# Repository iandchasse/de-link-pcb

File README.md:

# Silkscreen

**An open-source, open-hardware e-reader base board.**
Display-agnostic · case-agnostic · firmware-agnostic · battery-agnostic.

Successor to [de-link](https://de-link.me). Designed in **KiCad 9.0.6**.

Silkscreen is a base board for e-ink development: one 2-layer PCB that aims to drive
essentially any 24-pin SPI e-paper panel, from any battery, in any enclosure, under any
firmware — so the interesting work (display, case, software) isn't gated on redesigning power
and interface electronics every time.

Current full plots: **[schematic PDF](docs/silkscreen_pcb_schematic.pdf)** ·
**[PCB PDF](docs/silkscreen_pcb.pdf)**.

---

## At a glance

| | |
|---|---|
| **MCU** | ESP32-S3-WROOM-1 (**N8R8**, 8 MB octal PSRAM), native USB — no UART bridge |
| **Display** | 24-pin 0.5 mm ZIF for SPI e-paper; primary target 4.26" GDEQ426T82 family; panel-driven charge pump generates the ±15–22 V rails |
| **Frontlight** | TPS923610 constant-current boost, warm/cool CCT blending via a single GPIO + inverter |
| **Touch** | Optional I²C capacitive touch (for `-FT01C`-class panels) with a 0 Ω pin-swap mux |
| **Power** | USB-C in → TP4056 charger → DW01A + FS8205A cell protection → TPS2116 priority mux → TLV75533P 3V3 LDO |
| **Battery** | Bring-your-own single-cell LiPo; full on-board protection makes a bare cell safe |
| **Storage** | microSD in 4-bit SDMMC, power-gated |
| **Input** | 8 buttons on two ADC resistor ladders + power/boot/reset |
| **RTC** | DS3231MZ (±2 ppm), VBAT-only mode |
| **Board** | 2-layer, 60 × 111 mm, 1 oz Cu, 173 components |

Full block-by-block description: **[docs/HARDWARE.md](docs/HARDWARE.md)**.
Schematic review, margins and design rationale: **[DESIGN_REVIEW.md](DESIGN_REVIEW.md)**.

---

## Repository layout

```
silkscreen_pcb.kicad_pro / .kicad_sch / .kicad_pcb   KiCad 9 project
sym-lib-table / fp-lib-table                          project-local library tables
KiCad/9.0/3rdparty/                                   vendored symbols/footprints/3D models
docs/HARDWARE.md                                      hardware documentation
DESIGN_REVIEW.md                                      schematic + layout review
fabrication/                                          BOM, assembly data, how-to (gerbers gitignored)
LICENSE                                               CERN-OHL-S v2
```

## Building the board

You need **KiCad 9.0.x** (the files are 9.0 format; opening in 10.x upgrades them one-way).

### Fabrication (bare board)

Generate a gerber + drill set (JLCPCB, PCBWay and NextPCB all accept the same standard set):

```bash
kicad-cli pcb export gerbers -o fabrication/gerbers/ \
  --layers F.Cu,B.Cu,F.Mask,B.Mask,F.SilkS,B.SilkS,F.Paste,B.Paste,Edge.Cuts \
  --no-protel-ext --subtract-soldermask silkscreen_pcb.kicad_pcb
kicad-cli pcb export drill -o fabrication/gerbers/ --format excellon \
  --drill-origin absolute --excellon-units mm --excellon-separate-th silkscreen_pcb.kicad_pcb
```

Zip `fabrication/gerbers/` and upload. Board is 2-layer, 1.6 mm, 1 oz copper; outline on `Edge.Cuts`.

### Assembly

```bash
kicad-cli pcb export pos -o fabrication/assembly/cpl.csv --format csv --units mm --side both silkscreen_pcb.kicad_pcb
```

- **JLCPCB:** prefer the KiCad **Fabrication Toolkit** plugin — it applies JLC's part-rotation
  database and fills LCSC part numbers automatically. See [`fabrication/README.md`](fabrication/README.md).
- **PCBWay / NextPCB:** upload the gerber zip + the centroid + [`fabrication/BOM.csv`](fabrication/BOM.csv);
  they quote against the manufacturer part numbers.

See **[fabrication/README.md](fabrication/README.md)** for the full per-house process and caveats.

## Bill of materials

**[fabrication/BOM.md](fabrication/BOM.md)** — full BOM with manufacturers, MPNs, DigiKey/LCSC
links, LCSC-cheaper alternates, and per-part pricing with quantity break costs (board + a
"complete build" section covering PCB fab, display and battery).

## Documentation

- **[docs/HARDWARE.md](docs/HARDWARE.md)** — how every block works, GPIO map, design themes.
- **[DESIGN_REVIEW.md](DESIGN_REVIEW.md)** — net-by-net schematic review, margin analysis, and
  the layout spot-review.

---

## License

Hardware licensed under the **CERN Open Hardware Licence Version 2 – Strongly Reciprocal
(CERN-OHL-S-2.0)** — see [LICENSE](LICENSE).

> Copyright © 2026 idc LLC.
> This source describes Open Hardware and is licensed under the CERN-OHL-S v2.
> You may redistribute and modify this source and make products using it under the terms of the
> CERN-OHL-S v2 (https://ohwr.org/cern_ohl_s_v2.txt). This source is distributed WITHOUT ANY
> EXPRESS OR IMPLIED WARRANTY, INCLUDING OF MERCHANTABILITY, SATISFACTORY QUALITY AND FITNESS FOR
> A PARTICULAR PURPOSE. Please see the CERN-OHL-S v2 for applicable conditions.

`SPDX-License-Identifier: CERN-OHL-S-2.0`

Third-party component library files (from SnapEDA / Ultra Librarian / SamacSys) retain their own
terms and are not covered by the project license — see
[fabrication/THIRD_PARTY.md](fabrication/THIRD_PARTY.md).

Predecessor project: [de-link.me](https://de-link.me).

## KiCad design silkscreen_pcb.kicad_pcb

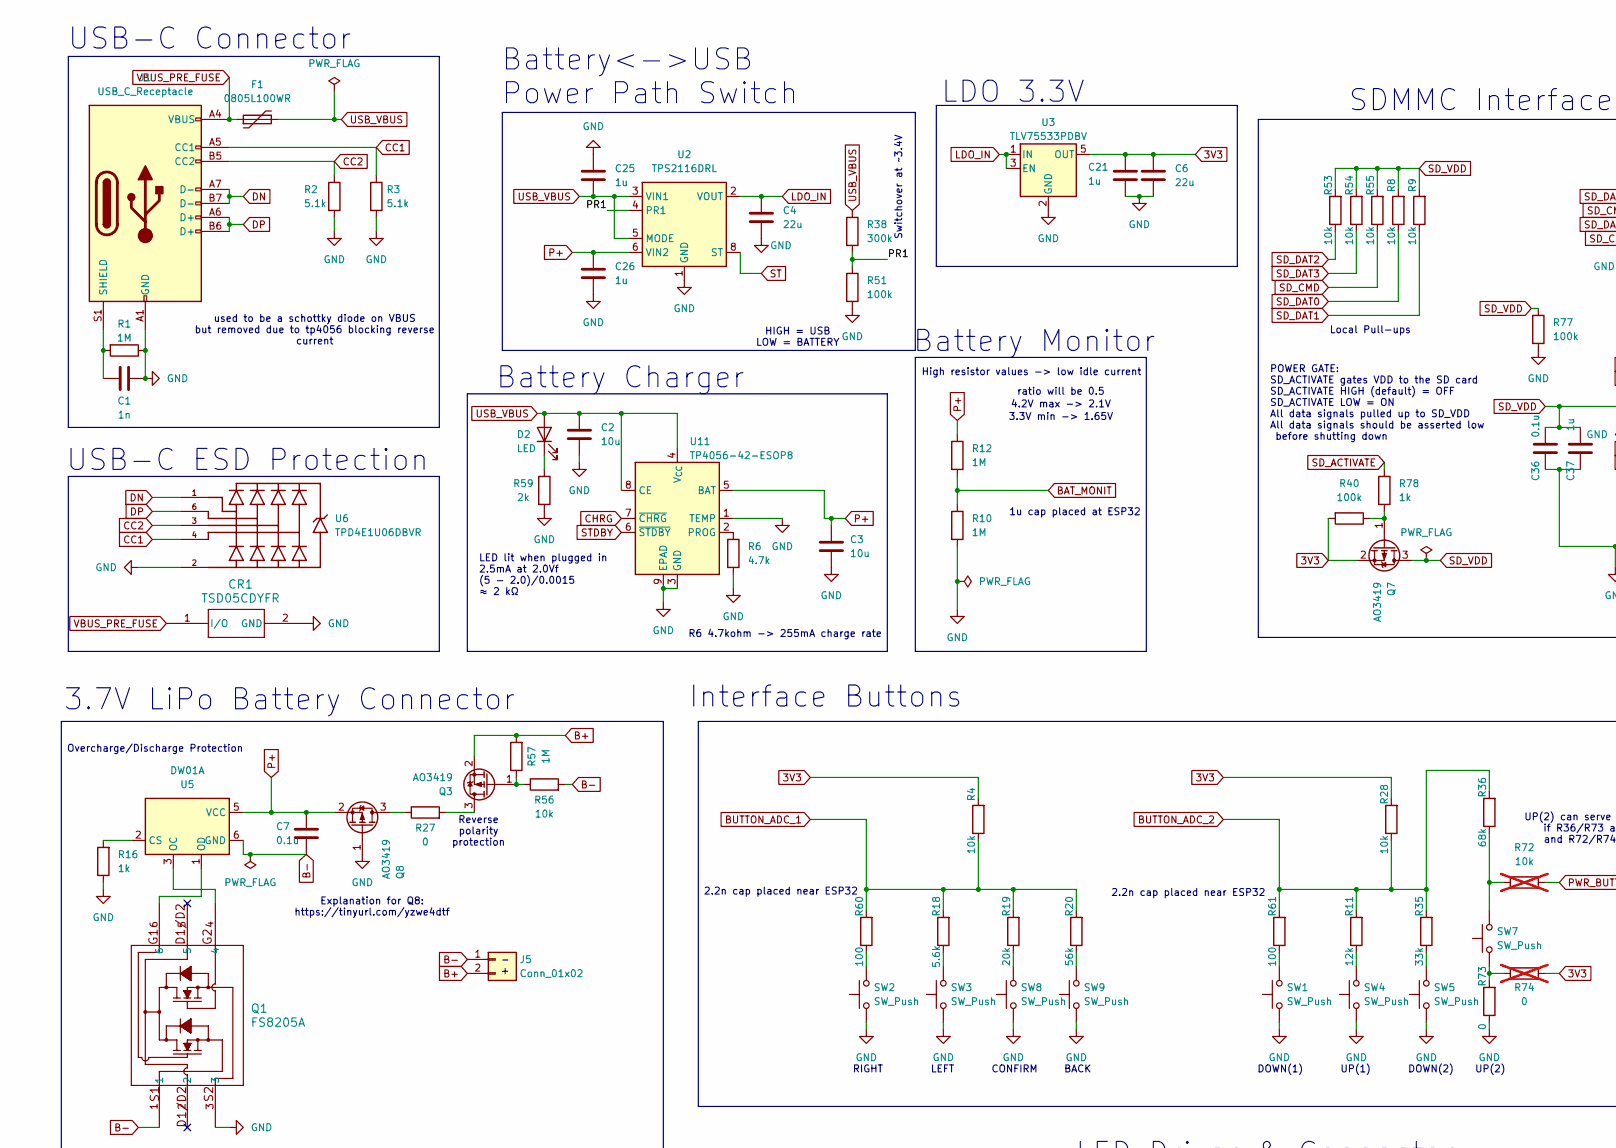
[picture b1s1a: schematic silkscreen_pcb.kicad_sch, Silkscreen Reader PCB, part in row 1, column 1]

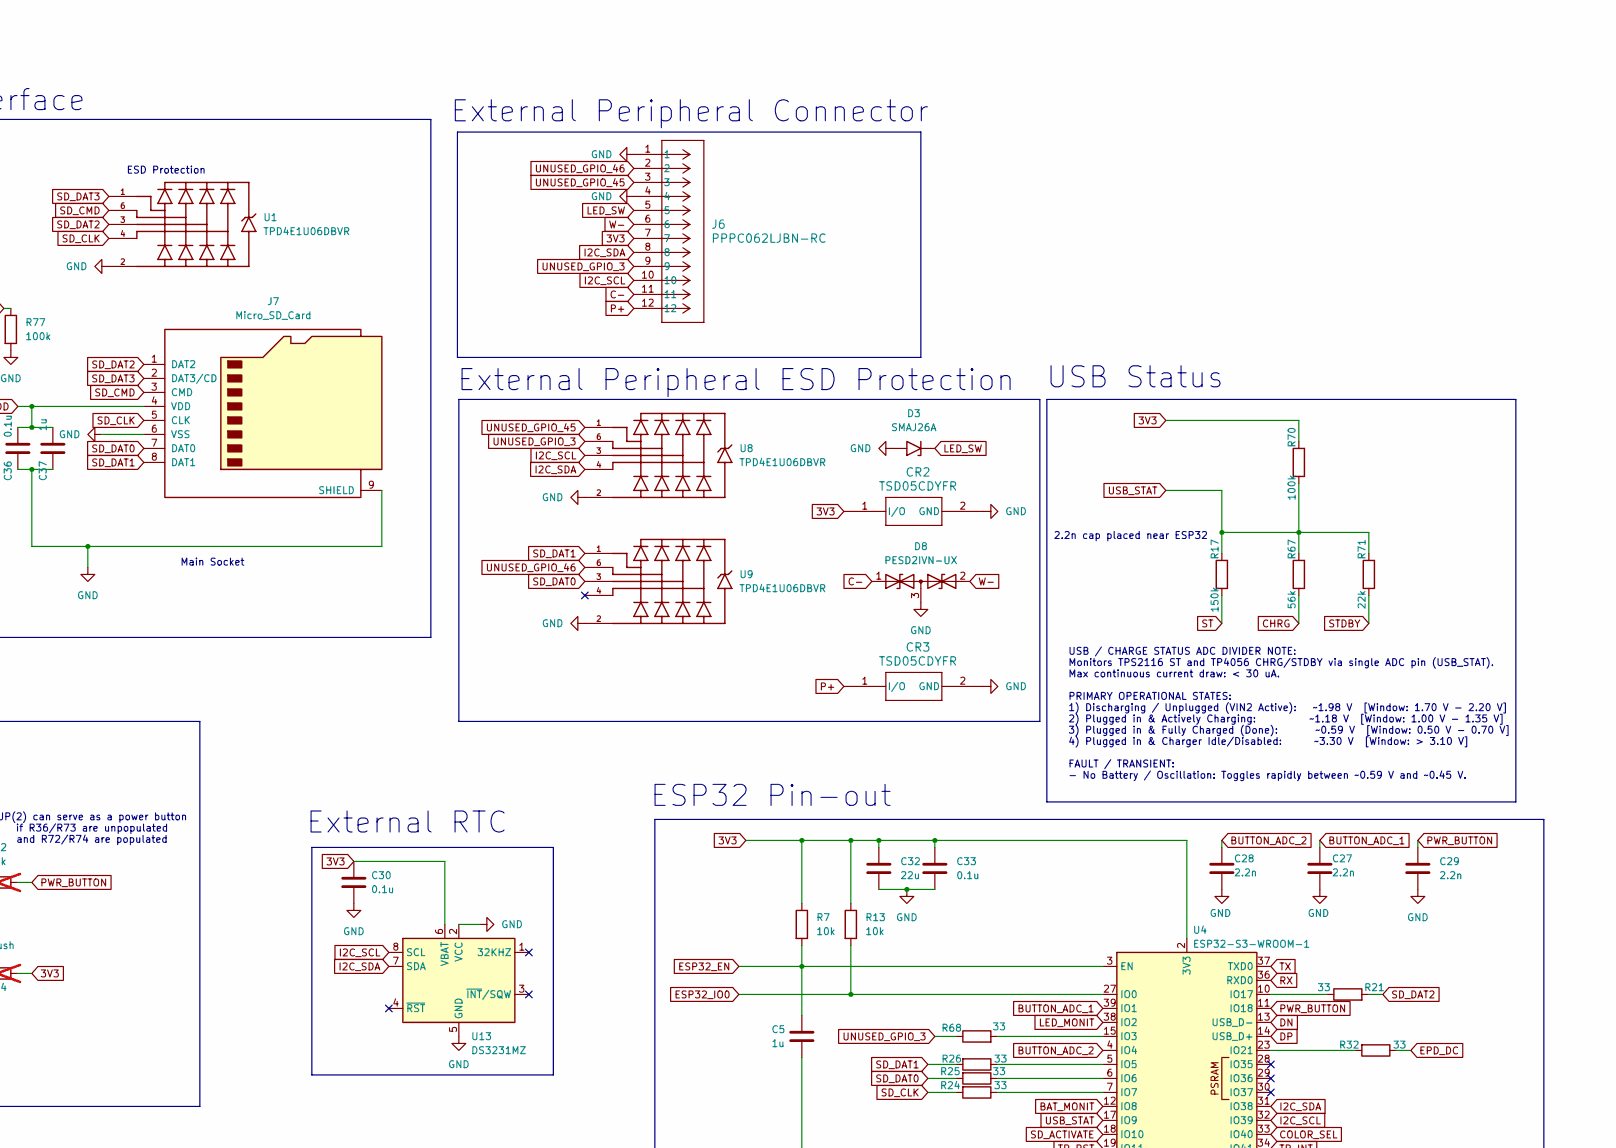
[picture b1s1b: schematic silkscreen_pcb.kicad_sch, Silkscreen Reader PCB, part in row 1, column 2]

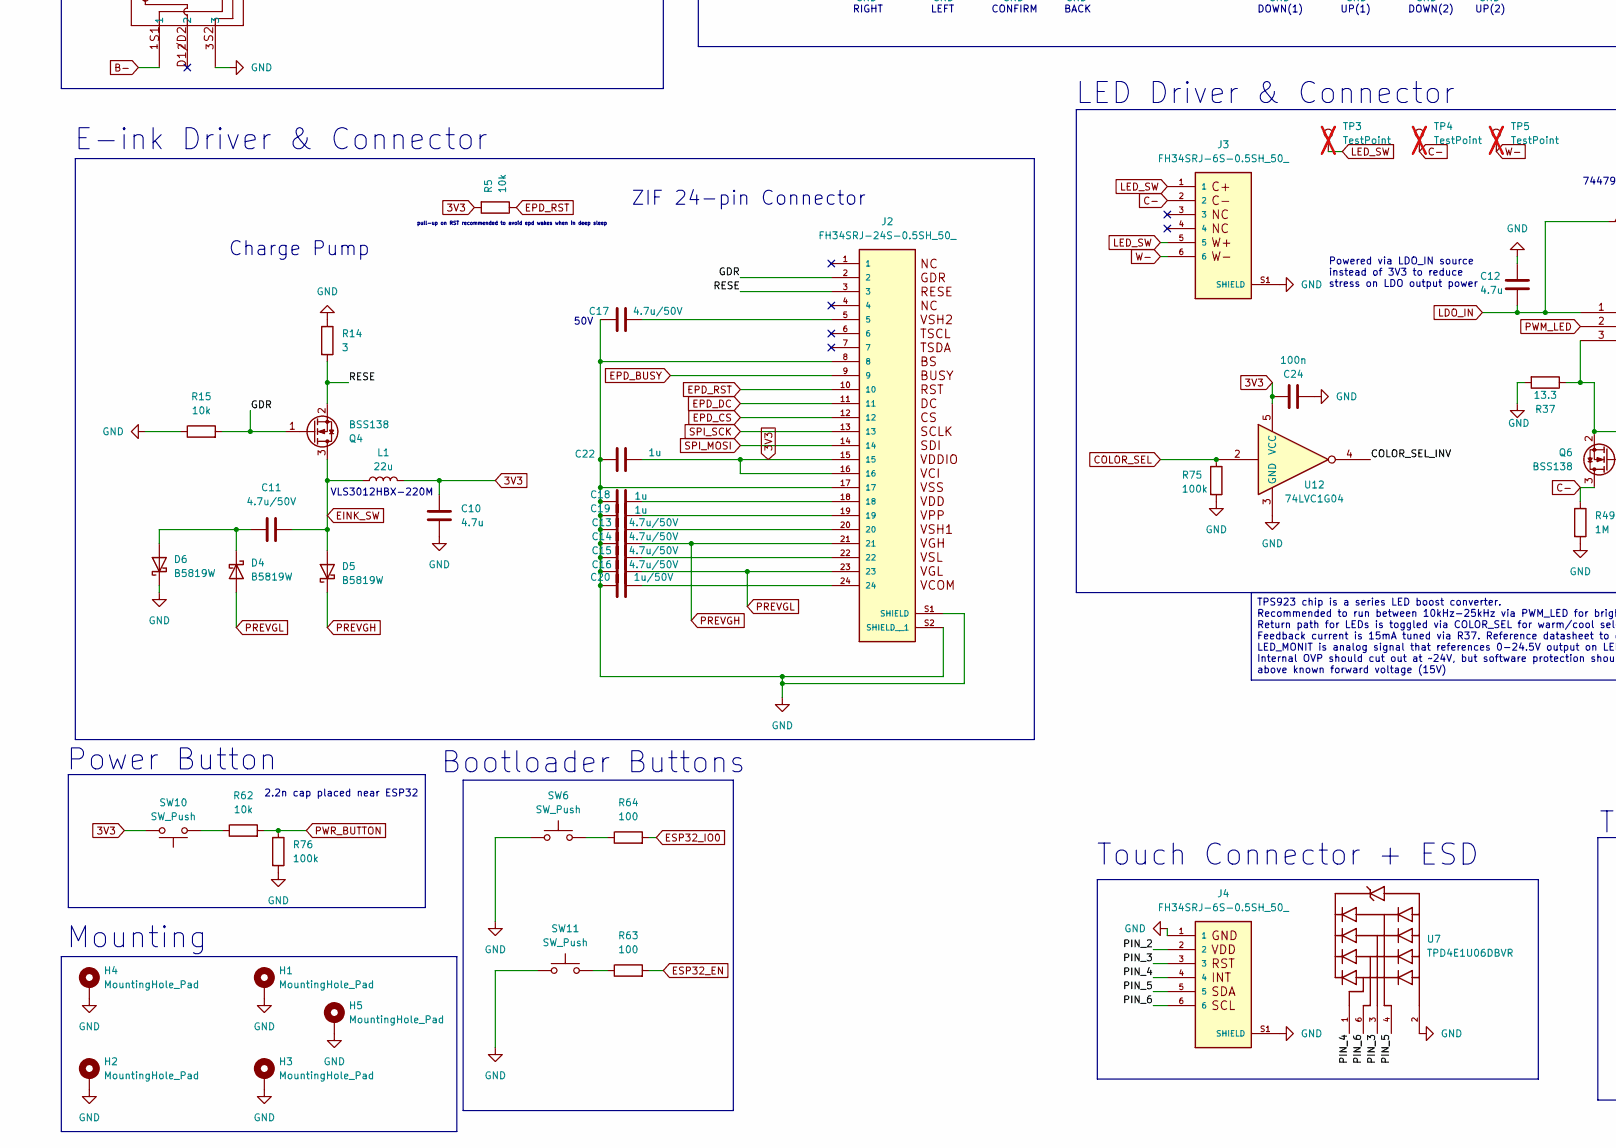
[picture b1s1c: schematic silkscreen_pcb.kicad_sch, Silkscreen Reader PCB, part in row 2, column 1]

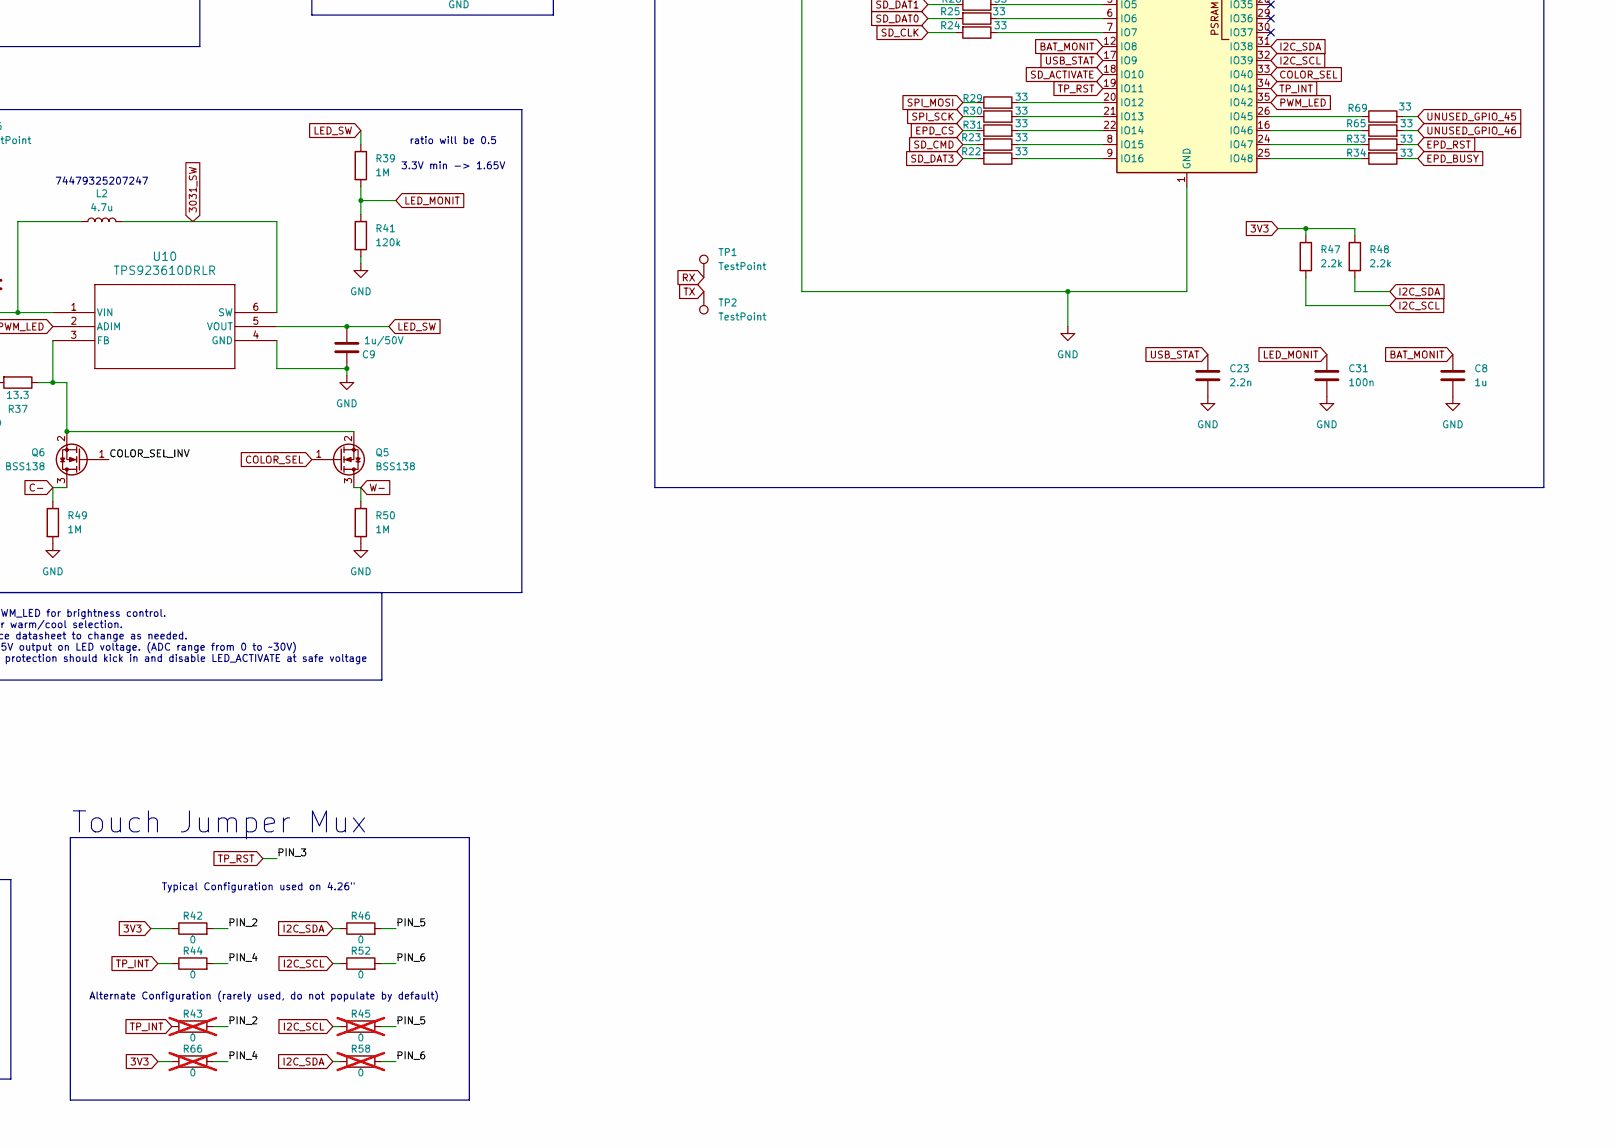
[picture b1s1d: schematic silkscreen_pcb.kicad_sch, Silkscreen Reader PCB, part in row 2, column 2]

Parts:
C1: 1n; C_0603_1608Metric_Pad1.08x0.95mm_HandSolder
C2, C3: 10u; C_0603_1608Metric_Pad1.08x0.95mm_HandSolder
C4, C6, C32: 22u; C_0805_2012Metric_Pad1.18x1.45mm_HandSolder
C5, C8, C21, C22, C25, C26, C37: 1u; C_0603_1608Metric_Pad1.08x0.95mm_HandSolder
C7, C30, C33, C36: 0.1u; C_0603_1608Metric_Pad1.08x0.95mm_HandSolder
C9, C20: 1u/50V; C_0805_2012Metric_Pad1.18x1.45mm_HandSolder
C10, C12: 4.7u; C_0603_1608Metric_Pad1.08x0.95mm_HandSolder
C11, C13, C14, C15, C16, C17: 4.7u/50V; C_0805_2012Metric_Pad1.18x1.45mm_HandSolder
C18, C19: 1u; C_0805_2012Metric_Pad1.18x1.45mm_HandSolder
C23, C27, C28, C29: 2.2n; C_0603_1608Metric_Pad1.08x0.95mm_HandSolder
C24, C31: 100n; C_0603_1608Metric_Pad1.08x0.95mm_HandSolder
CR1, CR2, CR3: TSD05CDYFR; D_SOD-323_HandSoldering
D2: LED; LED_1206_3216Metric_Pad1.42x1.75mm_HandSolder
D3: SMAJ26A; D_SMA
D4, D5, D6: B5819W; D_SOD-123
D8: PESD2IVN-UX; SOT-323_SC-70_Handsoldering
F1: 0805L100WR; Fuse_0805_2012Metric_Pad1.15x1.40mm_HandSolder
H1, H2, H3, H4, H5: MountingHole_Pad; MountingHole_2.2mm_M2_DIN965_Pad_TopBottom
J1: USB_C_Receptacle; USB_C_Receptacle_GCT_USB4085
J2: FH34SRJ-24S-0.5SH_50_; HRS_FH34SRJ-24S-0.5SH_50_
J3, J4: FH34SRJ-6S-0.5SH_50_; HRS_FH34SRJ-6S-0.5SH_50_; DigiKey_Part_Number H125773CT-ND
J5: Conn_01x02; JST_PH_S2B-PH-K_1x02_P2.00mm_Horizontal
J6: PPPC062LJBN-RC; CONN_PPPC062LJBN-RC_SUL
J7: Micro_SD_Card; microSD_HC_Hirose_DM3AT-SF-PEJM5
L1: 22u; IND_SRN3010C-100M
L2: 4.7u; L_1008_2520Metric_Pad1.43x2.20mm_HandSolder
Q1: FS8205A; SOT-23-6_Handsoldering
Q3, Q7, Q8: AO3419; SOT-23_Handsoldering
Q4, Q5, Q6: BSS138; SOT-23
R1, R10, R12, R39, R49, R50, R57: 1M; R_0603_1608Metric_Pad0.98x0.95mm_HandSolder
R2, R3: 5.1k; R_0603_1608Metric_Pad0.98x0.95mm_HandSolder
R4, R5, R7, R8, R9, R13, R15, R28, R53, R54, R55, R56, R62: 10k; R_0603_1608Metric_Pad0.98x0.95mm_HandSolder
R6: 4.7k; R_0603_1608Metric_Pad0.98x0.95mm_HandSolder
R11: 12k; R_0603_1608Metric_Pad0.98x0.95mm_HandSolder
R14: 3; R_0603_1608Metric_Pad0.98x0.95mm_HandSolder
R16, R78: 1k; R_0603_1608Metric_Pad0.98x0.95mm_HandSolder
R17: 150k; R_0603_1608Metric_Pad0.98x0.95mm_HandSolder
R18: 5.6k; R_0603_1608Metric_Pad0.98x0.95mm_HandSolder
R19: 20k; R_0603_1608Metric_Pad0.98x0.95mm_HandSolder
R20, R67: 56k; R_0603_1608Metric_Pad0.98x0.95mm_HandSolder
R21, R22, R23, R24, R25, R26, R29, R30, R31, R32, R33, R34, R65, R68, R69: 33; R_0603_1608Metric_Pad0.98x0.95mm_HandSolder
R27, R42, R44, R46, R52, R73: 0; R_0603_1608Metric_Pad0.98x0.95mm_HandSolder
R35: 33k; R_0603_1608Metric_Pad0.98x0.95mm_HandSolder
R36: 68k; R_0603_1608Metric_Pad0.98x0.95mm_HandSolder
R37: 13.3; R_0603_1608Metric_Pad0.98x0.95mm_HandSolder
R38: 300k; R_0603_1608Metric_Pad0.98x0.95mm_HandSolder
R40, R51, R70, R75, R76, R77: 100k; R_0603_1608Metric_Pad0.98x0.95mm_HandSolder
R41: 120k; R_0603_1608Metric_Pad0.98x0.95mm_HandSolder
R43, R45, R58, R66, R74: 0; R_0603_1608Metric_Pad0.98x0.95mm_HandSolder; not fitted
R47, R48: 2.2k; R_0603_1608Metric_Pad0.98x0.95mm_HandSolder
R59: 2k; R_0603_1608Metric_Pad0.98x0.95mm_HandSolder
R60, R61, R63, R64: 100; R_0603_1608Metric_Pad0.98x0.95mm_HandSolder
R71: 22k; R_0603_1608Metric_Pad0.98x0.95mm_HandSolder
R72: 10k; R_0603_1608Metric_Pad0.98x0.95mm_HandSolder; not fitted
SW1, SW2, SW3, SW4, SW5, SW7, SW8, SW9, SW10, SW11: SW_Push; MJTP1117
SW6: SW_Push; SW_PUSH_1P1T_6x3.5mm_H4.3_APEM_MJTP1243
TP1, TP2: TestPoint; TestPoint_Pad_1.0x1.0mm
TP3, TP4, TP5: TestPoint; PinHeader_1x01_P2.54mm_Vertical; not fitted
U1, U6, U7, U8, U9: TPD4E1U06DBVR; SOT-23-6_Handsoldering; PARTREV D; DigiKey_Part_Number 296-35965-1-ND
U2: TPS2116DRL; SOT-583-8
U3: TLV75533PDBV; SOT-23-5_HandSoldering
U4: ESP32-S3-WROOM-1
U5: DW01A; SOT-23-6_Handsoldering
U10: TPS923610DRLR; U_DRL0006A_6L_TEX-M
U11: TP4056-42-ESOP8; SOIC-8-1EP_3.9x4.9mm_P1.27mm_EP2.41x3.3mm_ThermalVias
U12: 74LVC1G04; SOT-23-5_HandSoldering
U13: DS3231MZ; SOIC-8_3.9x4.9mm_P1.27mm

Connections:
3V3: C6.1, C10.2, C21.1, C22.2, C24.1, C30.1, C32.1, C33.1, CR2.1 (I/O), J2.15, J2.16, J6.7, L1.2, Q7.2 (S), R4.2, R5.2, R7.1, R13.1, R28.2, R40.2, R42.1, R47.1, R48.1, R66.1, R70.2, R74.1, SW10.2, U3.5 (OUT), U4.2 (3V3), U12.5 (VCC), U13.6 (VBAT)
3031_SW: L2.2, U10.6 (SW)
/COLOR_SEL_INV: Q6.1 (G), U12.4
/GDR: J2.2, Q4.1 (G), R15.2
/PIN_2: J4.2, R42.2, R43.2
/PIN_4: J4.4, R44.2, R66.2, U7.1
/PIN_5: J4.5, R45.2, R46.2, U7.4
/PIN_6: J4.6, R52.2, R58.2, U7.6
/PR1: R38.2, R51.1, U2.4 (PR1)
/RESE: J2.3, Q4.2 (S), R14.2
B+: J5.2, Q3.2 (S), R57.2
B-: C7.2, J5.1, Q1.1, R56.2, U5.6 (GND)
BAT_MONIT: C8.1, R10.1, R12.2, U4.12 (IO8)
BUTTON_ADC_1: C27.2, R4.1, R18.2, R19.2, R20.2, R60.2, U4.39 (IO1)
BUTTON_ADC_2: C28.2, R11.2, R28.1, R35.2, R36.2, R61.2, U4.4 (IO4)
C-: D8.1 (A1), J3.2, J6.11, Q6.3 (D), R49.1, TP4.1
CC1: J1.A5 (CC1), R3.1, U6.4
CC2: J1.B5 (CC2), R2.1, U6.3
CHRG: R67.1, U11.7 (~CHRG)
COLOR_SEL: Q5.1 (G), R75.1, U4.33 (IO40), U12.2
DN: J1.A7 (D-), J1.B7 (D-), U4.13 (USB_D-), U6.1
DP: J1.A6 (D+), J1.B6 (D+), U4.14 (USB_D+), U6.6
EINK_SW: C11.2, D5.2 (A), L1.1, Q4.3 (D)
EPD_BUSY: J2.9, R34.1
EPD_CS: J2.12, R31.1
EPD_DC: J2.11, R32.1
EPD_RST: J2.10, R5.1, R33.1
ESP32_EN: C5.1, R7.2, R63.2, U4.3 (EN)
ESP32_IO0: R13.2, R64.2, U4.27 (IO0)
GND: C1.1, C2.2, C3.2, C4.2, C5.2, C6.2, C8.2, C9.1, C10.1, C12.1, C13.1, C14.1, C15.1, C16.1, C17.1, C18.1, C19.1, C20.1, C21.2, C22.1, C23.2, C24.2, C25.1, C26.2, C27.1, C28.1, C29.2, C30.2, C31.2, C32.2, C33.2, C36.1, C37.1, CR1.2 (GND), CR2.2 (GND), CR3.2 (GND), D3.2 (A2), D6.1 (K), D8.3 (common), H1.1, H2.1, H3.1, H4.1, H5.1, J1.A1 (GND), J1.A12 (GND), J1.B1 (GND), J1.B12 (GND), J2.8, J2.17, J2.S1 (SHIELD), J2.S2 (SHIELD__1), J3.S1 (SHIELD), J3.S2 (SHIELD), J4.1, J4.S1 (SHIELD), J4.S2 (SHIELD), J6.1, J6.4, J7.6 (VSS), J7.9 (SHIELD), Q1.3, Q8.1 (G), R1.1, R2.2, R3.2, R6.2, R10.2, R14.1, R15.1, R16.1, R37.2, R41.2, R49.2, R50.2, R51.2, R59.2, R73.1, R75.2, R76.2, R77.2, SW1.1, SW2.1, SW3.1, SW4.1, SW5.1, SW6.1, SW8.1, SW9.1, SW11.1, U1.2, U2.1 (GND), U3.2 (GND), U4.1 (GND), U4.40 (GND), U4.41 (GND), U6.2, U7.2, U8.2, U9.2, U10.4 (GND), U11.1 (TEMP), U11.3 (GND), U11.9 (EPAD), U12.3 (GND), U13.2 (VCC), U13.5 (GND)
I2C_SCL: J6.10, R45.1, R47.2, R52.1, U4.32 (IO39), U8.3, U13.8 (SCL)
I2C_SDA: J6.8, R46.1, R48.2, R58.1, U4.31 (IO38), U8.4, U13.7 (SDA)
LDO_IN: C4.1, C12.2, L2.1, U2.2 (VOUT), U2.7 (VOUT), U3.1 (IN), U3.3 (EN), U10.1 (VIN)
LED_MONIT: C31.1, R39.2, R41.1, U4.38 (IO2)
LED_SW: C9.2, D3.1 (A1), J3.1, J3.5, J6.5, R39.1, TP3.1, U10.5 (VOUT)
unnamed: C13.2, J2.20
unnamed: C15.2, J2.22
unnamed: C17.2, J2.5
unnamed: C18.2, J2.18
unnamed: C19.2, J2.19
unnamed: C20.2, J2.24
unnamed: D2.1 (K), R59.1
unnamed: C11.1, D4.1 (K), D6.2 (A)
unnamed: C1.2, J1.S1 (SHIELD), R1.2
unnamed: Q3.3 (D), R27.2
unnamed: Q3.1 (G), R56.1, R57.1
unnamed: Q5.2 (S), Q6.2 (S), R37.1, U10.3 (FB)
unnamed: Q7.1 (G), R40.1, R78.2
unnamed: Q8.3 (D), R27.1
unnamed: R11.1, SW4.2
unnamed: R18.1, SW3.2
unnamed: R19.1, SW8.2
unnamed: R20.1, SW9.2
unnamed: R35.1, SW5.2
unnamed: R36.1, R72.2, SW7.2
unnamed: R60.1, SW2.2
unnamed: R61.1, SW1.2
unnamed: R62.1, SW10.1
unnamed: R63.1, SW11.2
unnamed: R64.1, SW6.2
unnamed: R73.2, R74.2, SW7.1
unnamed: R68.2, U4.15 (IO3)
unnamed: R26.1, U4.5 (IO5)
unnamed: R25.1, U4.6 (IO6)
unnamed: R24.1, U4.7 (IO7)
unnamed: R29.2, U4.20 (IO12)
unnamed: R30.2, U4.21 (IO13)
unnamed: R31.2, U4.22 (IO14)
unnamed: R23.1, U4.8 (IO15)
unnamed: R22.1, U4.9 (IO16)
unnamed: R21.1, U4.10 (IO17)
unnamed: R32.2, U4.23 (IO21)
unnamed: R69.1, U4.26 (IO45)
unnamed: R65.1, U4.16 (IO46)
unnamed: R33.2, U4.24 (IO47)
unnamed: R34.2, U4.25 (IO48)
unnamed: R16.2, U5.2 (CS)
unnamed: Q1.4, U5.3 (OC)
unnamed: Q1.6, U5.1 (OD)
unnamed: R6.1, U11.2 (PROG)
P+: C3.1, C7.1, C26.1, CR3.1 (I/O), J6.12, Q8.2 (S), R12.1, U2.6 (VIN2), U5.5 (VCC), U11.5 (BAT)
PREVGH: C14.2, D5.1 (K), J2.21
PREVGL: C16.2, D4.2 (A), J2.23
PWM_LED: U4.35 (IO42), U10.2 (ADIM)
PWR_BUTTON: C29.1, R62.2, R72.1, R76.1, U4.11 (IO18)
RX: TP1.1, U4.36 (RXD0)
SD_ACTIVATE: R78.1, U4.18 (IO10)
SD_CLK: J7.5 (CLK), R24.2, U1.4
SD_CMD: J7.3 (CMD), R23.2, R55.1, U1.6
SD_DAT0: J7.7 (DAT0), R8.1, R25.2, U9.3
SD_DAT1: J7.8 (DAT1), R9.1, R26.2, U9.1
SD_DAT2: J7.1 (DAT2), R21.2, R53.1, U1.3
SD_DAT3: J7.2 (DAT3/CD), R22.2, R54.1, U1.1
SD_VDD: C36.2, C37.2, J7.4 (VDD), Q7.3 (D), R8.2, R9.2, R53.2, R54.2, R55.2, R77.1
SPI_MOSI: J2.14, R29.1
SPI_SCK: J2.13, R30.1
ST: R17.1, U2.8 (ST)
STDBY: R71.1, U11.6 (~STDBY)
TP_INT: R43.1, R44.1, U4.34 (IO41)
TP_RST: J4.3, U4.19 (IO11), U7.3
TX: TP2.1, U4.37 (TXD0)
UNUSED_GPIO_3: J6.9, R68.1, U8.6
UNUSED_GPIO_45: J6.3, R69.2, U8.1
UNUSED_GPIO_46: J6.2, R65.2, U9.6
USB_STAT: C23.1, R17.2, R67.2, R70.1, R71.2, U4.17 (IO9)
USB_VBUS: C2.1, C25.2, D2.2 (A), F1.2, R38.1, U2.3 (VIN1), U2.5 (MODE), U11.4 (V_{CC}), U11.8 (CE)
VBUS_PRE_FUSE: CR1.1 (I/O), F1.1, J1.A4 (VBUS), J1.A9 (VBUS), J1.B4 (VBUS), J1.B9 (VBUS)
W-: D8.2 (A2), J3.6, J6.6, Q5.3 (D), R50.1, TP5.1

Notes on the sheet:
Overcharge/Discharge Protection
ratio will be 0.5
USB / CHARGE STATUS ADC DIVIDER NOTE: Monitors TPS2116 ST and TP4056 CHRG/STDBY via single ADC pin (USB_STAT). Max continuous current draw: < 30 uA. PRIMARY OPERATIONAL STATES: 1) Discharging / Unplugged (VIN2 Active): ~1.98 V [Window: 1.70 V - 2.20 V] 2) Plugged in & Actively Charging: ~1.18 V [Wi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
SDMMC Interface
LED lit when plugged in 2.5mA at 2.0Vf (5 − 2.0)/0.0015 ≈ 2 kΩ
Battery<->USB Power Path Switch
RIGHT LEFT CONFIRM BACK
3.7V LiPo Battery Connector
Charge Pump
LED Driver & Connector
External RTC
2.2n cap placed near ESP32
Touch Connector + ESD
Touch Jumper Mux
VLS3012HBX-220M
Interface Buttons
3.3V min -> 1.65V
- +
pull-up on RST recommended to avoid epd wakes when in deep sleep
HIGH = USB LOW = BATTERY
POWER GATE: SD_ACTIVATE gates VDD to the SD card SD_ACTIVATE HIGH (default) = OFF SD_ACTIVATE LOW = ON All data signals pulled up to SD_VDD All data signals should be asserted low before shutting down
External Peripheral Connector
External Peripheral ESD Protection
E-ink Driver & Connector
74479325207247
ESD Protection
Battery Charger
50V
Typical Configuration used on 4.26"
ESP32 Pin-out
1u cap placed at ESP32
Reverse polarity protection
4.2V max -> 2.1V
ZIF 24-pin Connector
Local Pull-ups
DOWN(1) UP(1) DOWN(2) UP(2)
LDO 3.3V
USB Status
Power Button
High resistor values -> low idle current

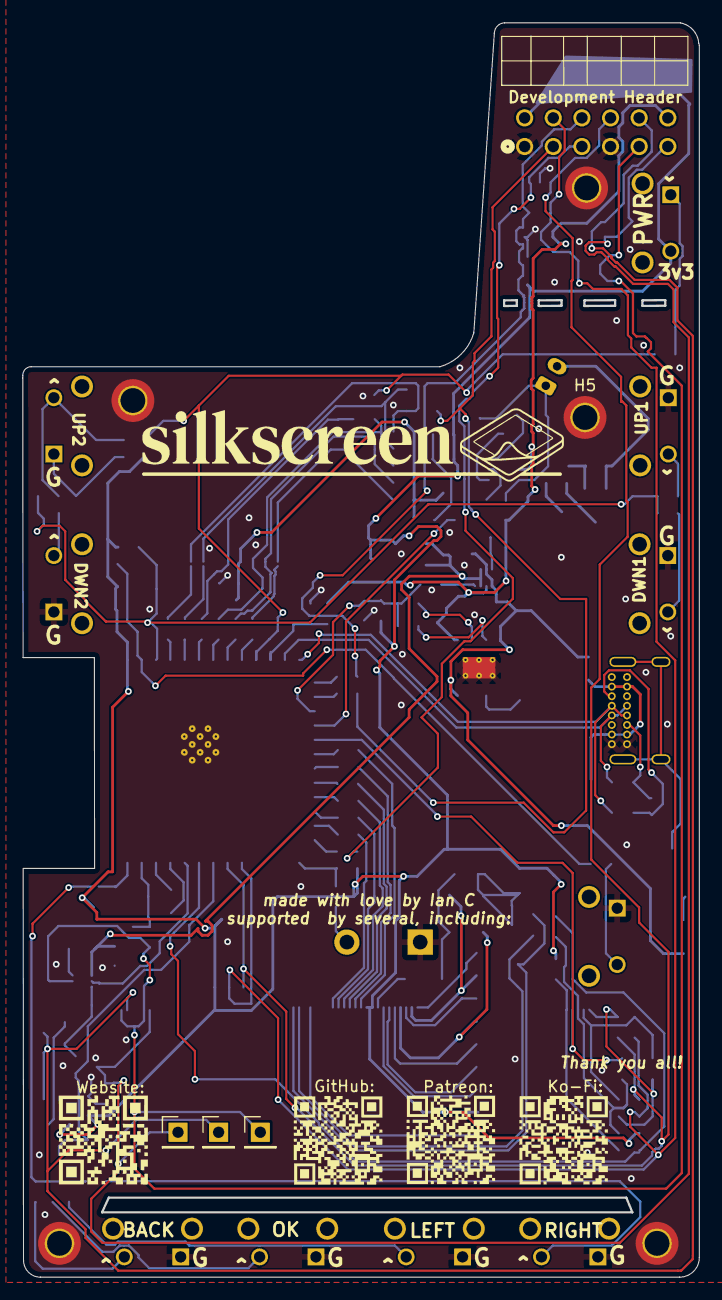
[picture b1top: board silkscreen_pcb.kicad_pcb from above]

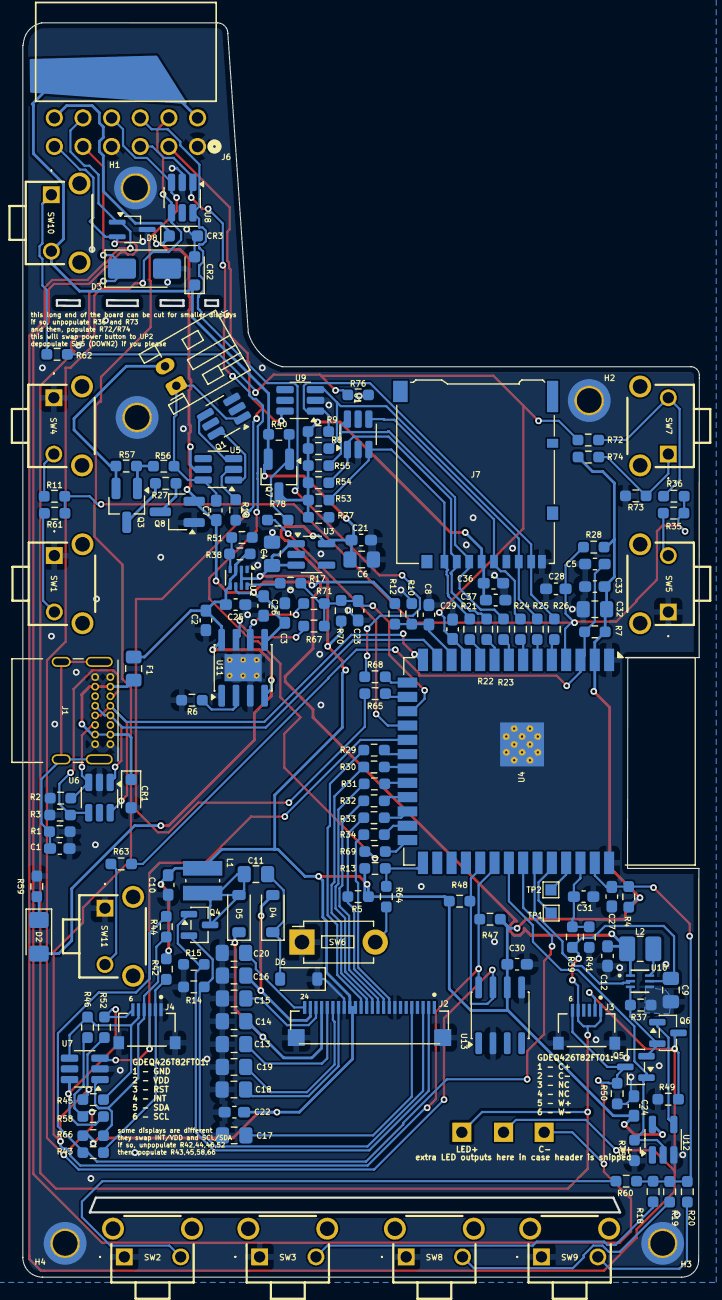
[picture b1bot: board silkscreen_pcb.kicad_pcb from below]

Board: 2 copper layers, 60.0 x 111.3 mm, 173 parts (169 on the bottom side), 108 nets.

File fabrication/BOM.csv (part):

Qty,Designators,Value,Footprint,Manufacturer,MPN,LCSC alt,Unit USD,Ext USD,Price src,DigiKey,DNP,Notes
1,U12,74LVC1G04,SOT-23-5_HandSoldering,Texas Instruments,SN74LVC1G04DBVR,,0.10,0.10,est,https://www.digikey.com/en/products/result?keywords=SN74LVC1G04DBVR,,inverter
1,U13,DS3231MZ,SOIC-8_3.9x4.9mm_P1.27mm,Analog Devices,DS3231MZ+,LCSC clone (e.g. C9866) far cheaper,5.50,5.50,est,https://www.digikey.com/en/products/result?keywords=DS3231MZ%2B,,RTC
1,U5,DW01A,SOT-23-6_Handsoldering,Fortune,DW01A,,0.10,0.10,ODS,https://www.digikey.com/en/products/result?keywords=DW01A,,LCSC C8724; source LCSC
1,U4,ESP32-S3-WROOM-1,ESP32-S3-WROOM-1,Espressif,ESP32-S3-WROOM-1-N8R8,N16R8 (more flash),5.66,5.66,ODS,https://www.digikey.com/en/products/result?keywords=ESP32-S3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,,octal-PSRAM; must be N8R8
1,U3,TLV75533PDBV,SOT-23-5_HandSoldering,Texas Instruments,TLV75533PDBVR,,0.35,0.35,est,https://www.digikey.com/en/products/result?keywords=TLV75533PDBVR,,3.3V LDO
1,U11,TP4056-42-ESOP8,SOIC-8-1EP_3.9x4.9mm_P1.27mm_EP2.41x3.3mm_ThermalVias,Nanjing Extension,TP4056-42-ESOP8,,0.15,0.15,est,https://www.digikey.com/en/products/result?keywords=TP4056-42-ESOP8,,LCSC C382139; source LCSC
5,U1 U6 U7 U8 U9,TPD4E1U06DBVR,SOT-23-6_Handsoldering,Texas Instruments,TPD4E1U06DBVR,,0.86,4.30,ODS,https://www.digikey.com/en/products/result?keywords=296-35965-1-ND,,
1,U2,TPS2116DRL,SOT-583-8,Texas Instruments,TPS2116DRL,,0.60,0.60,est,https://www.digikey.com/en/products/result?keywords=TPS2116DRL,,power-path mux
1,U10,TPS923610DRLR,U_DRL0006A_6L_TEX-M,Texas Instruments,TPS923610DRLR,,0.70,0.70,est,https://www.digikey.com/en/products/result?keywords=TPS923610DRLR,,frontlight boost
1,J5,Conn_01x02,JST_PH_S2B-PH-K_1x02_P2.00mm_Horizontal,JST,B2B-PH-K-S(LF)(SN),A2001WR-2P (LCSC PH equiv),0.15,0.15,est,https://www.digikey.com/en/products/result?keywords=B2B-PH-K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,,2p PH
1,J2,FH34SRJ-24S-0.5SH_50_,HRS_FH34SRJ-24S-0.5SH_50_,Hirose,FH34SRJ-24S-0.5SH(50),,2.26,2.26,ODS,https://www.digikey.com/en/products/result?keywords=FH34SRJ-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,,24p ZIF
2,J3 J4,FH34SRJ-6S-0.5SH_50_,HRS_FH34SRJ-6S-0.5SH_50_,Hirose,FH34SRJ-6S-0.5SH(50),,0.79,1.58,ODS,https://www.digikey.com/en/products/result?keywords=H125773CT-ND,,
1,J7,Micro_SD_Card,microSD_HC_Hirose_DM3AT-SF-PEJM5,Hirose,DM3AT-SF-PEJM5,,2.86,2.86,ODS,https://www.digikey.com/en/products/result?keywords=DM3AT-SF-PEJM5,,microSD
1,J6,PPPC062LJBN-RC,CONN_PPPC062LJBN-RC_SUL,Sullins,PPPC062LJBN-RC,"A2541HWR-2x6P (LCSC, if OOS)",1.50,1.50,est,https://www.digikey.com/en/products/result?keywords=PPPC062LJBN-RC,,2x6 header
1,J1,USB_C_Receptacle,USB_C_Receptacle_GCT_USB4085,GCT,USB4085-GF-A-060,,0.91,0.91,ODS,https://www.digikey.com/en/products/result?keywords=USB4085-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,,USB-C; verify suffix
3,Q3 Q7 Q8,AO3419,SOT-23_Handsoldering,Alpha & Omega,AO3419,IRLML6402,0.49,1.47,ODS,https://www.digikey.com/en/products/result?keywords=AO3419,,
3,Q4 Q5 Q6,BSS138,SOT-23,onsemi,BSS138LT1G,,0.31,0.93,ODS,https://www.digikey.com/en/products/result?keywords=BSS138LT1G,,
1,Q1,FS8205A,SOT-23-6_Handsoldering,Fortune,FS8205A,,0.39,0.39,ODS,https://www.digikey.com/en/products/result?keywords=FS8205A,,LCSC C32254
3,D4 D5 D6,B5819W,D_SOD-123,MCC,B5819W,,0.22,0.66,ODS,https://www.digikey.com/en/products/result?keywords=B5819W,,equiv 1N5819HW-7-F
1,D2,LED,LED_1206_3216Metric_Pad1.42x1.75mm_HandSolder,,LED 1206,,0.10,0.10,est,,,power indicator
1,D8,PESD2IVN-UX,SOT-323_SC-70_Handsoldering,Nexperia,PESD2IVN-UX,,0.20,0.20,est,https://www.digikey.com/en/products/result?keywords=PESD2IVN-UX,,ESD
1,D3,SMAJ26A,D_SMA,Littelfuse,SMAJ26A,,0.30,0.30,est,https://www.digikey.com/en/products/result?keywords=SMAJ26A,,TVS
3,CR1 CR2 CR3,TSD05CDYFR,D_SOD-323_HandSoldering,Texas Instruments,TSD05CDYFR,GOODWORK SD05C,0.67,2.01,ODS,https://www.digikey.com/en/products/result?keywords=TSD05CDYFR,,
1,L1,22u,IND_SRN3010C-100M,TDK,VLS3012HBX-220M,,0.50,0.50,est,https://www.digikey.com/en/products/result?keywords=VLS3012HBX-220M,,22uH shielded
1,L2,4.7u,L_1008_2520Metric_Pad1.43x2.20mm_HandSolder,Wurth Elektronik,74479325207247,,0.30,0.30,est,https://www.digikey.com/en/products/result?keywords=74479325207247,,4.7uH WE-LQS 1008
1,F1,0805L100WR,Fuse_0805_2012Metric_Pad1.15x1.40mm_HandSolder,Littelfuse,0805L100WR,,0.30,0.30,est,https://www.digikey.com/en/products/result?keywords=0805L100WR,,1.0A PPTC
10,SW1 SW2 SW3 SW4 SW5 SW7 SW8 SW9 SW10 SW11,SW_Push,MJTP1117,APEM,MJTP1117,"SKHLLAA010 / TS365ZJ (cheaper, LCSC)",0.12,1.20,est,https://www.digikey.com/en/products/result?keywords=MJTP1117,,6mm tactile
1,SW6,SW_Push,SW_PUSH_1P1T_6x3.5mm_H4.3_APEM_MJTP1243,APEM,MJTP1243,,0.20,0.20,est,https://www.digikey.com/en/products/result?keywords=MJTP1243,,6x3.5mm tactile
6,R27 R42 R44 R46 R52 R73,0,R_0603_1608Metric_Pad0.98x0.95mm_HandSolder,,RES 0 0603,,0.10,0.60,ODS,https://www.digikey.com/en/products/result?keywords=RES%200%200603,,0 ohm jumper
5,R43 R45 R58 R66 R74,0,R_0603_1608Metric_Pad0.98x0.95mm_HandSolder,,RES 0 0603,,0.10,0.50,ODS,https://www.digikey.com/en/products/result?keywords=RES%200%200603,DNP,0 ohm jumper
4,R60 R61 R63 R64,100,R_0603_1608Metric_Pad0.98x0.95mm_HandSolder,,RES 100 0603,,0.10,0.40,ODS,https://www.digikey.com/en/products/result?keywords=RES%2010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,,
6,R40 R51 R70 R75 R76 R77,100k,R_0603_1608Metric_Pad0.98x0.95mm_HandSolder,,RES 100k 0603,,0.10,0.60,ODS,https://www.digikey.com/en/products/result?keywords=RES%2010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,,
13,R4 R5 R7 R8 R9 R13 R15 R28 R53 R54 R55 R56 R62,10k,R_0603_1608Metric_Pad0.98x0.95mm_HandSolder,,RES 10k 0603,,0.10,1.30,ODS,https://www.digikey.com/en/products/result?keywords=RES%2010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,,
1,R72,10k,R_0603_1608Metric_Pad0.98x0.95mm_HandSolder,,RES 10k 0603,,0.10,0.10,ODS,https://www.digikey.com/en/products/result?keywords=RES%2010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,DNP,
1,R41,120k,R_0603_1608Metric_Pad0.98x0.95mm_HandSolder,,RES 120k 0603,,0.10,0.10,ODS,https://www.digikey.com/en/products/result?keywords=RES%2012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,,
1,R11,12k,R_0603_1608Metric_Pad0.98x0.95mm_HandSolder,,RES 12k 0603,,0.10,0.10,ODS,https://www.digikey.com/en/products/result?keywords=RES%2012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,,
1,R37,13.3,R_0603_1608Metric_Pad0.98x0.95mm_HandSolder,,RES 13.3 0603,,0.10,0.10,ODS,https://www.digikey.com/en/products/result?keywords=RES%2013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,,
1,R17,150k,R_0603_1608Metric_Pad0.98x0.95mm_HandSolder,,RES 150k 0603,,0.10,0.10,ODS,https://www.digikey.com/en/products/result?keywords=RES%2015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,,
7,R1 R10 R12 R39 R49 R50 R57,1M,R_0603_1608Metric_Pad0.98x0.95mm_HandSolder,,RES 1M 0603,,0.10,0.70,ODS,https://www.digikey.com/en/products/result?keywords=RES%201M%200603,,
2,R16 R78,1k,R_0603_1608Metric_Pad0.98x0.95mm_HandSolder,,RES 1k 0603,,0.10,0.20,ODS,https://www.digikey.com/en/products/result?keywords=RES%201k%200603,,
2,R47 R48,2.2k,R_0603_1608Metric_Pad0.98x0.95mm_HandSolder,,RES 2.2k 0603,,0.10,0.20,ODS,https://www.digikey.com/en/products/result?keywords=RES%202.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,,
1,R19,20k,R_0603_1608Metric_Pad0.98x0.95mm_HandSolder,,RES 20k 0603,,0.10,0.10,ODS,https://www.digikey.com/en/products/result?keywords=RES%2020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,,
1,R71,22k,R_0603_1608Metric_Pad0.98x0.95mm_HandSolder,,RES 22k 0603,,0.10,0.10,ODS,https://www.digikey.com/en/products/result?keywords=RES%2022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,,
1,R59,2k,R_0603_1608Metric_Pad0.98x0.95mm_HandSolder,,RES 2k 0603,,0.10,0.10,ODS,https://www.digikey.com/en/products/result?keywords=RES%202k%200603,,
1,R14,3,R_0603_1608Metric_Pad0.98x0.95mm_HandSolder,,RES 3 0603,,0.10,0.10,ODS,https://www.digikey.com/en/products/result?keywords=RES%203%200603,,
1,R38,300k,R_0603_1608Metric_Pad0.98x0.95mm_HandSolder,,RES 300k 0603,,0.10,0.10,ODS,https://www.digikey.com/en/products/result?keywords=RES%2030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,,
15,R21 R22 R23 R24 R25 R26 R29 R30 R31 R32 R33 R34 R65 R68 R69,33,R_0603_1608Metric_Pad0.98x0.95mm_HandSolder,,RES 33 0603,,0.10,1.50,ODS,https://www.digikey.com/en/products/result?keywords=RES%2033%200603,,
1,R35,33k,R_0603_1608Metric_Pad0.98x0.95mm_HandSolder,,RES 33k 0603,,0.10,0.10,ODS,https://www.digikey.com/en/products/result?keywords=RES%2033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,,
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

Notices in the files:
silkscreen_pcb.kicad_pcb:
Licensed under CERN-OHL-S-2.0
